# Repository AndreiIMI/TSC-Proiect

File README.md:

# TSC-Proiect
## Schema Bloc

## BOM (Bill of Materials)
| Component                            | Link | Datasheet |
|--------------------------------------|------|-----------|
| ESP32-C6-WROOM-1-N8                  | [Link](https://ro.mouser.com/ProductDetail/Espressif-Systems/ESP32-C6-WROOM-1-N8?qs=8Wlm6%252BaMh8ST02Gmwp74cw%3D%3D) | [Datasheet](https://ro.mouser.com/datasheet/2/891/Espressif_ESP32_C6_WROOM_1__Datasheet_V0_1_PRELIMI-3239987.pdf) |
| 112A-TAAR-R03_ATTEND                 | [Link](https://www.digikey.ro/ro/products/detail/attend-technology/112A-TAAR-R03/17633923) | [Datasheet](https://www.attend.com.tw/data/download/file/112A-TAAR-R03_Spec.pdf) |
| ADAFRUIT_LEDCHIP-LED0603            | [Link](https://www.snapeda.com/parts/KP-1608SURCK/Kingbright/view-part/?ref=search&t=LED%200603) | [Datasheet](https://www.snapeda.com/parts/KP-1608SURCK/Kingbright/datasheet/) |
| ESP32_WROVER_EAGLE-LTSPICE_RR0402   | [Link](https://www.snapeda.com/parts/RC0402FR-07226RL/Yageo/view-part/) | [Datasheet](https://www.snapeda.com/parts/RC0402FR-07226RL/Yageo/datasheet/) |
| ESP32_WROVER_EAGLE-LTSPICE_CC0402   | [Link](https://componentsearchengine.com/part-view/CC0402MRX5R5BB106/YAGEO) | [Datasheet](https://componentsearchengine.com/Datasheets/2/CC0402MRX5R5BB106.pdf) |
| RCL_CPOL-EUCT3528                   | [Link](https://ro.mouser.com/ProductDetail/Vishay-Sprague/TR3B106K025C1300?qs=jCGqFXxTmLdffnuDkXzk1g%3D%3D) | [Datasheet](https://www.vishay.com/docs/40080/tr3.pdf) |
| ESP32_WROVER_SPARKFUN-DISCRETESEMI_MOSFET_PCH-DMG2305UX-7 | [Link](https://ro.mouser.com/ProductDetail/Diodes-Incorporated/DMG2305UX-7?qs=L1DZKBg7t5F%2FNBHrjfxC%252Bg%3D%3D) | [Datasheet](https://www.diodes.com/assets/Datasheets/DMG2305UX.pdf) |
| 744043680IND_4828-WE-TPC_WRE        | [Link](https://www.digikey.sg/en/products/detail/w%C3%BCrth-elektronik/744043680/1638515) | [Datasheet](https://www.we-online.com/components/products/datasheet/744043680.pdf) |
| BD5229G-TR                          | [Link](https://ro.mouser.com/ProductDetail/ROHM-Semiconductor/BD5229G-TR?qs=4kLU8WoGk0vvnhrrYwdszw%3D%3D) | [Datasheet](https://fscdn.rohm.com/en/products/databook/datasheet/ic/power/voltage_detector/bd52xxg-e.pdf) |
| ESP32_WROVER_BME680_BME680          | [Link](https://ro.mouser.com/ProductDetail/Bosch-Sensortec/BME680?qs=v271MhAjFHjo0yA%2FC4OnDQ%3D%3D) | [Datasheet](https://ro.mouser.com/datasheet/2/783/BST_BME680_DS001-1509608.pdf) |
| BUTTON_CUSTOMV1                     | [Link](https://ro.mouser.com/ProductDetail/Panasonic/EVQ-P7M01P?qs=rJ%252BziJWpysz0sJAzuCybtw%3D%3D) | [Datasheet](https://industry.panasonic.com/global/en/downloads/?file_cd=402906&tab=catalog&series_cd=3457) |
| CPH3225A                             | [Link](https://ro.mouser.com/ProductDetail/Seiko-Semiconductors/CPH3225A?qs=3etwrb1wR%252BhUOph6lAO7eg%3D%3D) | [Datasheet](https://ro.mouser.com/datasheet/2/360/Seiko_Instruments_MicroBattery_E_20230330_2024Jan_-3561061.pdf) |
| DS3231SN#                            | [Link](https://ro.mouser.com/ProductDetail/Analog-Devices-Maxim-Integrated/DS3231SN?qs=1eQvB6Dk1vhUlr8%2FOrV0Fw%3D%3D) | [Datasheet](https://ro.mouser.com/datasheet/2/609/DS3231-3421123.pdf) |
| ESP32C6_VARISTORCN1812              | [Link](https://eu.mouser.com/ProductDetail/KEMET/VC1812L501R008?qs=jj7GbYRQuOa1j1%2F3gPpdvQ%3D%3D) | [Datasheet](https://eu.mouser.com/datasheet/2/447/KEM_V0002_VC-3316862.pdf) |
| ESP32_WROVER_AVX---SD0805S020S1R0_AVX_SD0805S020S1R0_0_0AVX_SD0805S020S1R0_0_0 | [Link](https://eu.mouser.com/ProductDetail/KYOCERA-AVX/SD0805S020S1R0?qs=jCA%252BPfw4LHbpkAoSnwrdjw%3D%3D&utm_id=6470900573&utm_source=google&utm_medium=cpc&utm_marketing_tactic=emeacorp&gad_source=1&gbraid=0AAAAADn_wf2CZaBvMXoqDoLB8a6wI1EC_&gclid=CjwKCAjw--K_BhB5EiwAuwYoyhyp4YPMQJxEs9O7Um1pbb_qrwD9UbwWFHYqYH_KvU5-nXs4CTfFVRoCY7kQAvD_BwE) | [Datasheet](https://eu.mouser.com/datasheet/2/40/schottky-3165252.pdf) |
| FH34SRJ-24S-0.5SH_99_               | [Link](https://eu.mouser.com/ProductDetail/Hirose-Connector/FH34SRJ-24S-05SH99?qs=vcbW%252B4%252BSTIpKBl5ap9J8Fw%3D%3D&utm_id=6470900573&utm_source=google&utm_medium=cpc&utm_marketing_tactic=emeacorp&gad_source=1&gbraid=0AAAAADn_wf2CZaBvMXoqDoLB8a6wI1EC_&gclid=CjwKCAjw--K_BhB5EiwAuwYoykKExbMK_Nf7-m2eYAFcWwWt_BaAKmDd5HmJ3DzOwus-MUIZVeL9ExoCTtAQAvD_BwE) | [Datasheet](https://eu.mouser.com/datasheet/2/185/FH34SRJ_24S_0_5SH_99__CL0580_1255_6_99_2DDrawing_0-1615044.pdf) |
| MAX17048G+T10                        | [Link](https://eu.mouser.com/ProductDetail/Analog-Devices-Maxim-Integrated/MAX17048G+T10?qs=D7PJwyCwLAoGnnn8jEPRBQ%3D%3D&utm_id=20109199409&utm_source=google&utm_medium=cpc&utm_marketing_tactic=emeacorp&gad_source=1&gbraid=0AAAAADn_wf23I7VSL8Khkvz-kjEhjYqPz&gclid=CjwKCAjw--K_BhB5EiwAuwYoytVFz576awyE1ug3GUFRWVeGavv1g_gzDMEDxxjVwp1JIOS60JmKnhoC-zIQAvD_BwE) | [Datasheet](https://eu.mouser.com/datasheet/2/609/MAX17048_MAX17049-3469099.pdf) |
| MBR0530                              | [Link](https://eu.mouser.com/ProductDetail/Micro-Commercial-Components-MCC/MBR0530-TP?qs=KFo7JewZbUECRHkxGanrdg%3D%3D&utm_id=6470900573&utm_source=google&utm_medium=cpc&utm_marketing_tactic=emeacorp&gad_source=1&gbraid=0AAAAADn_wf2CZaBvMXoqDoLB8a6wI1EC_&gclid=CjwKCAjw--K_BhB5EiwAuwYoysNC_AmHFOx6dFFFiTr86y8jRKC674aUhl0na6xIgHM9UWT_XyhG0RoCYwIQAvD_BwE) | [Datasheet](https://eu.mouser.com/datasheet/2/258/MBR0520_MBR0580_SOD123_-2492194.pdf) |
| ESP32_WROVER_SPARKFUN-IC-POWER_MCP73831 | [Link](https://ro.mouser.com/ProductDetail/Microchip-Technology/MCP73831-2DCI-MC?qs=hH%252BOa0VZEiBQ%2FrptDRXKdg%3D%3D) | [Datasheet](https://ro.mouser.com/datasheet/2/268/MCP73831_Family_Data_Sheet_DS20001984H-3441711.pdf) |
| PGB1010603MR                         | [Link](https://ro.mouser.com/ProductDetail/Littelfuse/PGB1010603MR?qs=gu7KAQ731URLg4GSnNNN7Q%3D%3D) | [Datasheet](https://www.littelfuse.com/assetdocs/pulseguard-esd-suppressors-pgb1-datasheet?assetguid=8a337998-d54d-466b-be4e-dc5bcd1f9321) |
| QWIIC_CONNECTORJS-1MM               | [Link](https://www.sparkfun.com/qwiic-jst-connector-smd-4-pin-vertical.html) | [Datasheet](https://www.jst-mfg.com/product/pdf/eng/eSH.pdf?5ec58813d214e) |
| SAMACSYS_PARTS_USB4110-GF-A         | [Link](https://eu.mouser.com/ProductDetail/GCT/USB4110-GF-A?qs=KUoIvG%2F9IlYiZvIXQjyJeA%3D%3D&utm_id=6470900573&utm_source=google&utm_medium=cpc&utm_marketing_tactic=emeacorp&gad_source=1&gbraid=0AAAAADn_wf2CZaBvMXoqDoLB8a6wI1EC_&gclid=CjwKCAjw--K_BhB5EiwAuwYoyqoFYku-1KEnaVMBZNhraqam0ThMUfxlrF7A4GQ8Pqj9d6zLqr7juBoCrOEQAvD_BwE) | [Datasheet](https://eu.mouser.com/datasheet/2/837/GCT_USB4110_Product_Drawing___20k_cycles-3455479.pdf) |
| SI1308EDL-T1-GE3                     | [Link](https://eu.mouser.com/ProductDetail/Vishay-Semiconductors/SI1308EDL-T1-GE3?qs=bX1%252BNvsK%2FBramh9tgpOaEw%3D%3D&utm_id=20109199409&utm_source=google&utm_medium=cpc&utm_marketing_tactic=emeacorp&gad_source=1&gbraid=0AAAAADn_wf23I7VSL8Khkvz-kjEhjYqPz&gclid=CjwKCAjw--K_BhB5EiwAuwYoyllRgbebqlW1QDUb9SQpEls061aMn76tZxer07jsniKXNOsDESHnSBoCkL8QAvD_BwE) | [Datasheet](https://www.vishay.com/docs/63399/si1308edl.pdf) |
| USBLC6-2SC6Y                         | [Link](https://eu.mouser.com/ProductDetail/STMicroelectronics/USBLC6-2SC6Y?qs=gNDSiZmRJS%2FOgDexvXkdow%3D%3D&srsltid=AfmBOoqlX0fgvKlHMd5oyRC9Sr6hBsf51Zi0RKmaIGejNRz6zsEP_LgY) | [Datasheet](https://eu.mouser.com/datasheet/2/389/usblc6_2sc6y-1852505.pdf) |
| SJ                                   | [Link](https://grabcad.com/library/solder-jumpers-1) | [Datasheet](https://github.com/cristiandeda/TSC_E-BookReader/blob/main) |
| W25Q512JVEIQ                         | [Link](https://eu.mouser.com/ProductDetail/Winbond/W25Q512JVEIQ?qs=l7cgNqFNU1jw6svr3at6tA%3D%3D&srsltid=AfmBOopwp-NQhQ6JM3w-WMYdzldr5QNIm_7CdLwVaaaS66y9swf4PMgu) | [Datasheet](https://eu.mouser.com/datasheet/2/949/Winbond_W25Q512JV_Datasheet-3240039.pdf) |
| XC6220A331MR-G                       | [Link](https://eu.mouser.com/ProductDetail/Torex-Semiconductor/XC6220A331MR-G?qs=AsjdqWjXhJ8ZSWznL1J0gg%3D%3D&srsltid=AfmBOopNlEzK7MdHRFabPSVSf32rb8GhsgKYTsuSlo8EjEXWvzOc5IIo) | [Datasheet](https://eu.mouser.com/datasheet/2/760/xc6220-3371556.pdf) |
## Descrierea funcționalității hardware
Această placă integrează multiple componente pentru a oferi o soluție completă de control, senzorizare și afișare cu consum redus, ideală pentru aplicații IoT.

### Alimentare și Încărcare
* #### Conector USB-C
  Oferă atât alimentare principală (5V), cât și comunicație de date.

* #### Regulator tensiune (IC1)
  Convertor step-down care aduce tensiunea de la 5V la 3.3V, necesară pentru alimentarea ESP32 și a celorlalte circuite logice.

* #### Protecție la supratensiuni (TVS - D1, PFMF.050.1)
  Diodă TVS care protejează linia de alimentare USB și comunicație împotriva descărcărilor electrostatice (ESD) și supratensiunilor.

* #### Control încărcare baterie (MCP73831)
  Circuit dedicat pentru încărcarea bateriilor Li-Po, cu protecție la supraîncărcare și descărcare. Condensatorii C1 și C2 filtrează zgomotul de pe linia de alimentare.

* #### Monitorizare baterie (MAX17048)
  Cititor de nivel al bateriei cu comunicație I2C, oferă date precise despre starea acumulatorului în timp real.

### Memorie și Stocare
* #### Memorie NOR Flash SPI (W25Q512JVEIQ)
  Stocare de 64MB pentru fișiere (imagini, texte, baze de date), conectată la ESP32 prin SPI.

* #### Cititor card SD
  Conectat pe interfață SPI (IO8–IO11), permite extinderea capacității de stocare, ideal pentru loguri sau import de fișiere externe.

### Control Principal - ESP32-C6
* #### Microcontroller ESP32-C6-WROOM-1-N8
  Nucleul principal al plăcii, gestionează toate perifericele. Suportă Wi-Fi 6, BLE 5.2, Zigbee și Thread. Dispune de GPIO-uri versatile pentru SPI, I2C, UART și control direct pentru afișajele e-paper.

### Ceas în Timp Real (RTC)
* #### DS3231SN
  Modul de ceas cu precizie ridicată, conectat prin I2C. Are o baterie de rezervă ce menține ora actualizată chiar și fără alimentare principală.

### Senzor Ambiental
* #### BME688
  Senzor avansat care măsoară temperatura, umiditatea, presiunea atmosferică și calitatea aerului. Comunicarea se face prin I2C.

### Afișaj E-Paper
* #### Header dedicat pentru E-Ink Display
  Permite conectarea unui afișaj e-paper cu consum ultra-redus.

* #### Circuit de control semnal (MBR0530, L1, Q3)
  Asigură comutarea corectă a tensiunii și semnalelor pentru afișaj.

* #### Selectare ecran
  Prin jumperul S1 se poate selecta tipul de e-paper utilizat.

### Interfețe Extinse
* #### Qwiic / Stemma QT
  Conector standard JST-SH cu 4 pini pentru adăugarea de senzori sau module I2C externe cu plug-and-play.

* #### Test Pads GPIO
  Paduri expuse pentru pini importanți ai ESP32. Ușurează depanarea, măsurătorile sau conectarea de periferice suplimentare.

### Protecție și Control
* #### Protecție ESD pe SPI & Qwiic
  Include diode TVS și rezistențe pentru protecția semnalelor împotriva descărcărilor electrostatice.

* #### Butoane de control (RESET & BOOT)
  RESET – repornește sistemul; BOOT – folosit pentru programarea ESP32. Ambele conectate la pini esențiali (EN și IO0).

## Descrierea Pinilor ESP32-C6

| **Pin ESP32-C6** | **Nume Semnal**         | **Componentă Asociată**         | **Scop / Funcție**                                                                 |
|------------------|--------------------------|----------------------------------|--------------------------------------------------------------------------------------|
| **GND**          | GND                      | Toate componentele               | Masă comună pentru alimentare și semnal.                                            |
| **EN**           | Enable                   | Buton Reset                      | Resetează microcontrollerul la apăsare.                                             |
| **IO0**          | GPIO0                    | Buton BOOT                       | Intrare în modul de boot la apăsare.                                                |

### Test & GPIO General

| **Pin ESP32-C6** | **Nume Semnal**         | **Componentă Asociată**         | **Scop / Funcție**                                                                 |
|------------------|--------------------------|----------------------------------|--------------------------------------------------------------------------------------|
| **IO1**          | GPIO1                    | Test Pad TP11                   | I/O general sau pentru debug.                                                       |
| **IO2**          | GPIO2                    | Test Pad TP12                   | I/O general sau pentru debug.                                                       |
| **IO3**          | GPIO3                    | Test Pad TP13                   | I/O general sau pentru debug.                                                       |

### Memorie NOR Flash (SPI)

| **Pin ESP32-C6** | **Nume Semnal**         | **Componentă Asociată**         | **Scop / Funcție**                                                                 |
|------------------|--------------------------|----------------------------------|--------------------------------------------------------------------------------------|
| **IO4**          | CS                       | SPI Flash (W25Q512JVEIQ)        | Chip Select pentru memoria externă.                                                |
| **IO5**          | CLK                      | SPI Flash                        | Clock SPI pentru NOR Flash.                                                        |
| **IO6**          | MISO                     | SPI Flash                        | Date din NOR Flash către ESP32.                                                    |
| **IO7**          | MOSI                     | SPI Flash                        | Date de la ESP32 către NOR Flash.                                                  |

### Card SD (SPI)

| **Pin ESP32-C6** | **Nume Semnal**         | **Componentă Asociată**         | **Scop / Funcție**                                                                 |
|------------------|--------------------------|----------------------------------|--------------------------------------------------------------------------------------|
| **IO8**          | CS                       | SD Card                          | Chip Select pentru card SD.                                                        |
| **IO9**          | CLK                      | SD Card                          | Clock SPI pentru card SD.                                                          |
| **IO10**         | MISO                     | SD Card                          | Date de pe card SD către ESP32.                                                    |
| **IO11**         | MOSI                     | SD Card                          | Date de la ESP32 către card SD.                                                    |

### E-Paper Display

| **Pin ESP32-C6** | **Nume Semnal**         | **Componentă Asociată**         | **Scop / Funcție**                                                                 |
|------------------|--------------------------|----------------------------------|--------------------------------------------------------------------------------------|
| **IO12**         | BUSY / RST / etc.        | E-Paper Header                   | Semnale de control pentru afișaj.                                                  |
| **IO13**         | -                        | E-Paper Header                   | Semnal suplimentar pentru afișaj.                                                  |
| **IO14**         | -                        | E-Paper Header                   | Semnal suplimentar pentru afișaj.                                                  |
| **IO15**         | -                        | E-Paper Header                   | Semnal suplimentar pentru afișaj.                                                  |

### Magistrală I2C (RTC & Senzor Mediu)

| **Pin ESP32-C6** | **Nume Semnal**         | **Componentă Asociată**         | **Scop / Funcție**                                                                 |
|------------------|--------------------------|----------------------------------|--------------------------------------------------------------------------------------|
| **IO16**         | SCL                      | RTC (DS3231), BME688             | Clock pentru comunicația I2C.                                                      |
| **IO17**         | SDA                      | RTC (DS3231), BME688             | Date pentru comunicația I2C.                                                       |

### Serial Debug / Qwiic

| **Pin ESP32-C6** | **Nume Semnal**         | **Componentă Asociată**         | **Scop / Funcție**                                                                 |
|------------------|--------------------------|----------------------------------|--------------------------------------------------------------------------------------|
| **IO18**         | UART_RX                  | Qwiic / Debug Header             | Recepție serială (ex: debugging, interfață Qwiic).                                  |
| **IO19**         | UART_TX                  | Qwiic / Debug Header             | Transmisie serială.                                                                 |

## Pași de Implementare

1. **Proiectarea Schemei**
   - Am realizat schema electrică folosind componente din biblioteca specificată.
   - Am verificat schema cu ERC și am rezolvat toate erorile relevante.
   - M-am asigurat că toate componentele au footprint corect și conexiuni valide.

2. **Plasarea Componentelor pe PCB**
   - Am plasat toate componentele exclusiv pe layer-ul **TOP**, conform cerințelor.
   - Am amplasat corect condensatoarele de decuplare (100nF) lângă pinii de alimentare.
   - Am poziționat antena modulului ESP32 spre exteriorul plăcii și am decupat zona de sub ea.
   - Am ignorat erorile de dimension generate de butoane și mufa USB, conform instrucțiunilor.

3. **Rutarea PCB-ului**
   - Am rutat traseele de alimentare cu **width = 0.3mm** și cele de semnal cu **minim 0.15mm**.
   - Am evitat unghiurile drepte și am minimizat utilizarea de vias-uri pe traseele de putere.
   - Fiind o placă dublu strat, am aplicat **via stitching** între planurile de masă.
   - Nu am rutat trasee sub antena ESP32 și am decupat zona PCB-ului din acea regiune.

4. **Verificare și Validare**
   - Am folosit fișierul de verificare pentru DRC și am corectat toate problemele importante.
   - Am ignorat eroarea “Only INPUT pins on NET ID” conform indicațiilor.
   - Am marcat clar toate test pad-urile în silkscreen cu denumirile semnalelor (ex. MOSI, RX).

5. **Realizarea Silkscreen-ului**
   - Am păstrat silkscreen-ul clar și lizibil, cu **numele componentelor**, fără valorile acestora.

6. **Modelarea 3D**
   - Am importat modelul 3D al PCB-ului în carcasa furnizată.
   - Am desenat bateria și ecranul conform dimensiunilor mecanice din datasheet-uri.

7. **Generarea Fișierelor Finale**
   - Am generat fișierele **Gerber** conform tutorialului oferit.
   - Am creat fișierele **BOM** și **Pick and Place** pentru fabricație, urmând pașii din tutorial.
   - Pentru componente și modele 3D, am folosit [Component Search Engine](https://componentsearchengine.com).

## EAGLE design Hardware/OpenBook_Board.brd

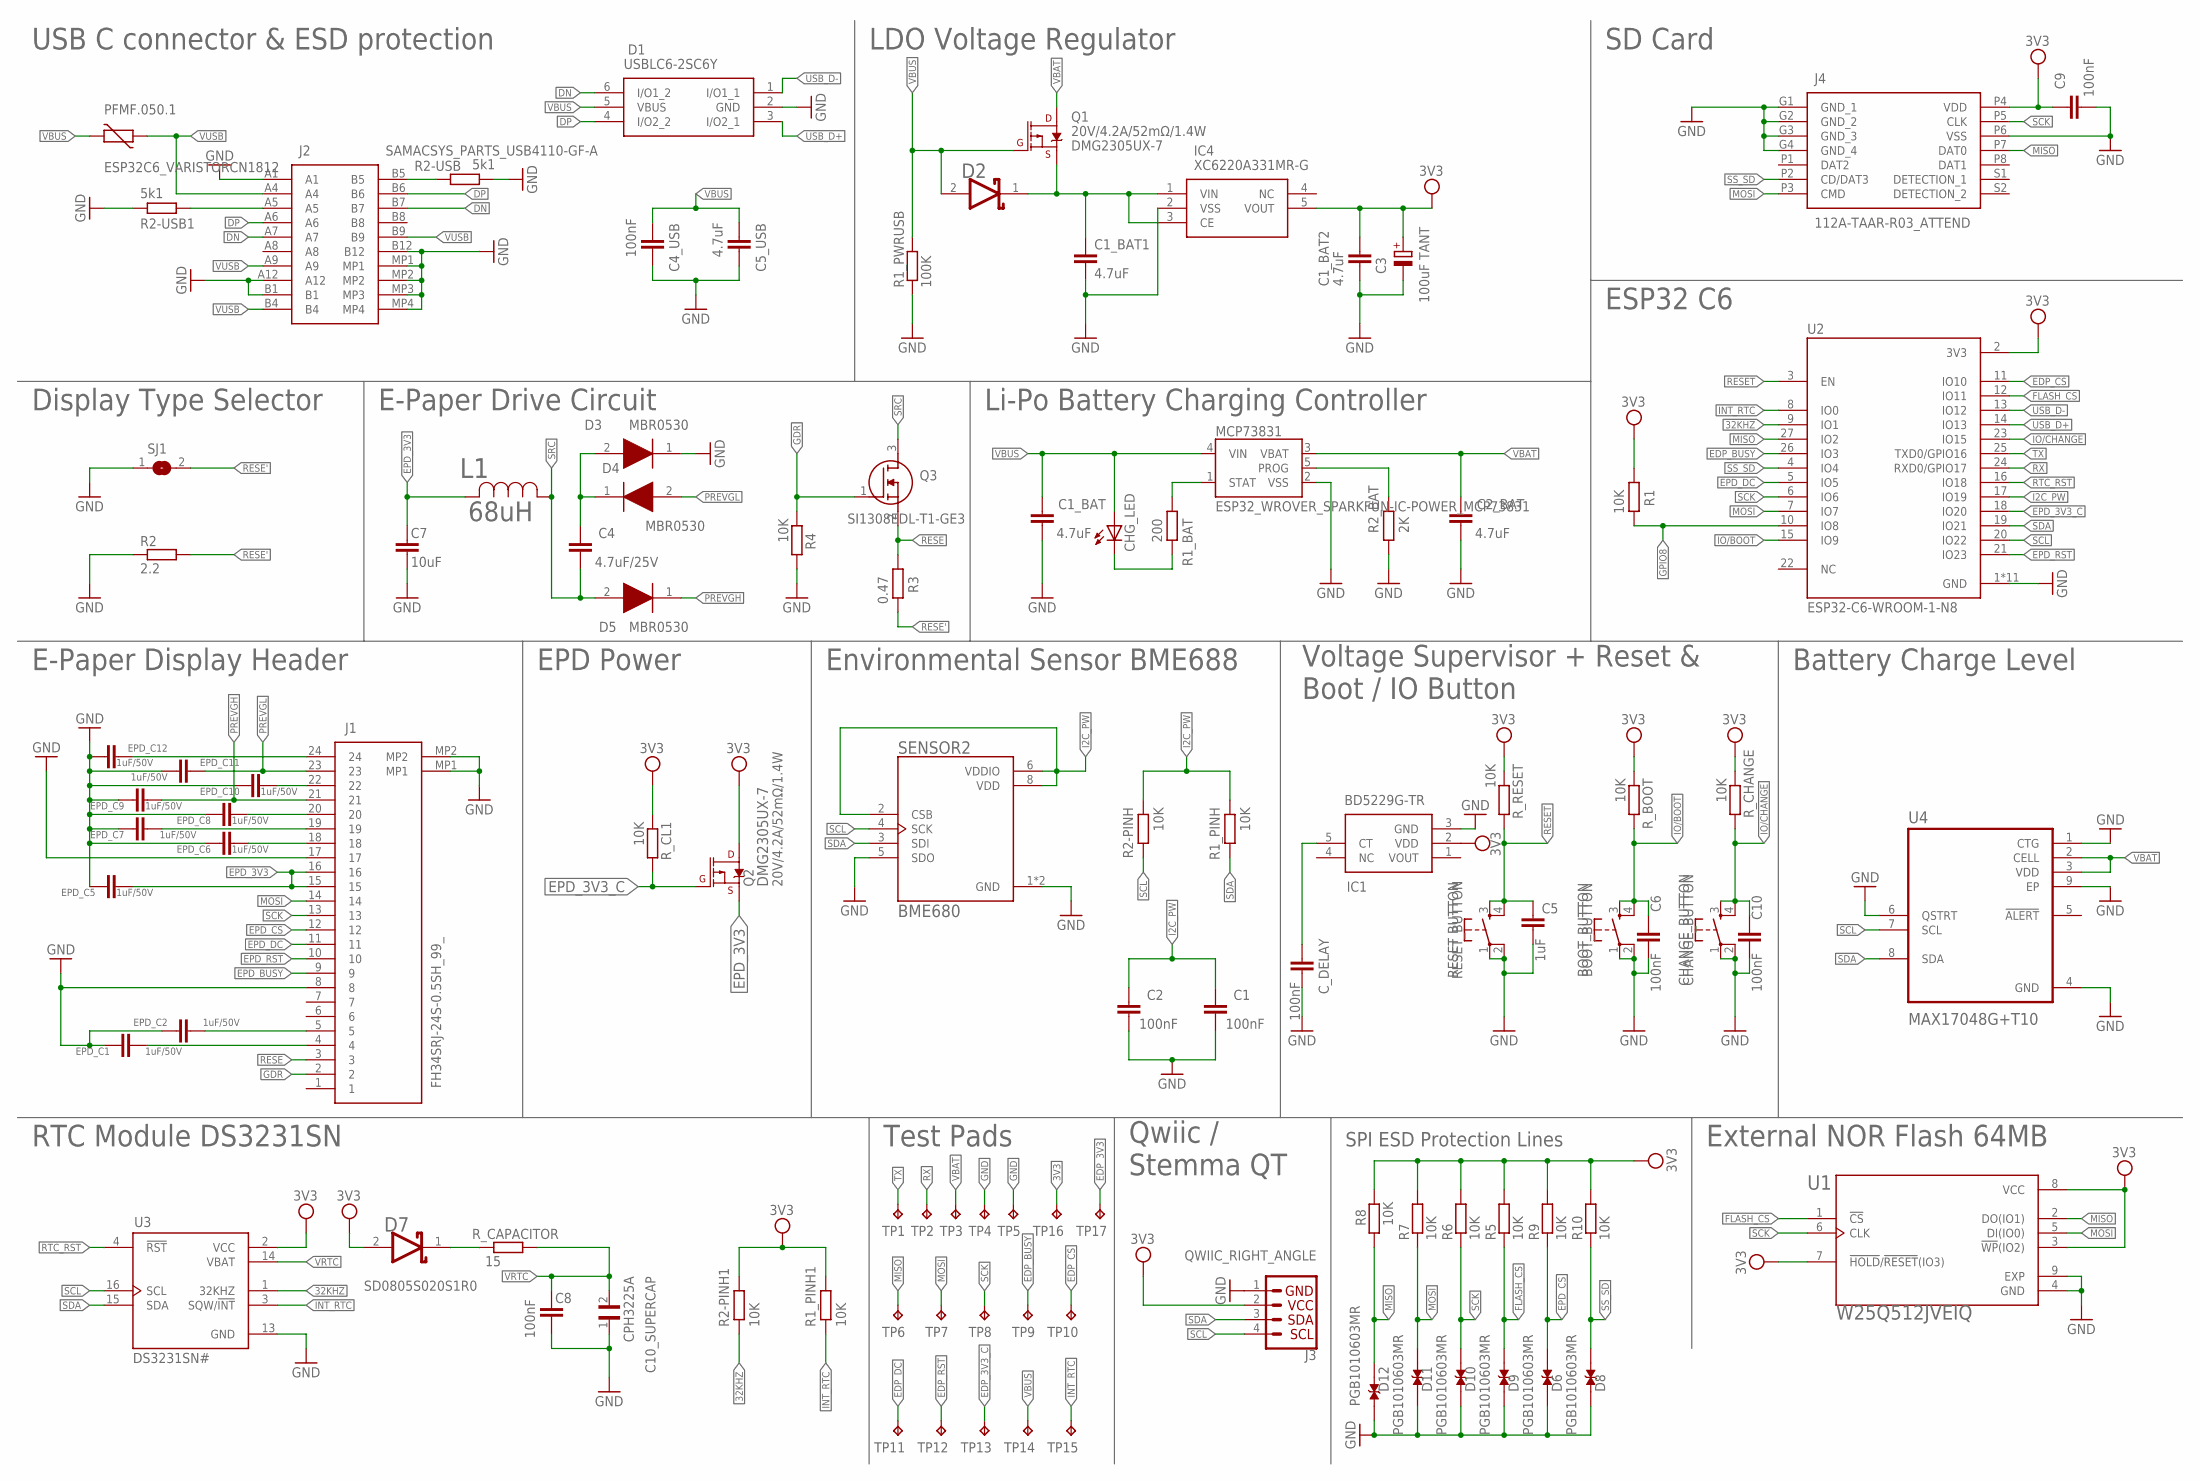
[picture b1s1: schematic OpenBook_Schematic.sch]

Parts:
BOOT_BUTTON: BOOT_BUTTON; MYBUTTON
C1, C2, C4_USB, C6, C8, C9, C10: 100nF; EAGLE-LTSPICE_C0402
C1_BAT, C1_BAT1, C1_BAT2, C2_BAT, C5_USB: 4.7uF; EAGLE-LTSPICE_C0402
C3: 100uF TANT; RCL_CT3528
C4: 4.7uF/25V; EAGLE-LTSPICE_C0402
C5: 1uF; EAGLE-LTSPICE_C0402
C7: 10uF; EAGLE-LTSPICE_C0402
C10_SUPERCAP: CPH3225A; CAPCP3225X100N
CHANGE_BUTTON: CHANGE_BUTTON; MYBUTTON
CHG_LED: ADAFRUIT_LEDCHIP-LED0603; ADAFRUIT_CHIP-LED0603
C_DELAY: 100nF; EAGLE-LTSPICE_C0402
D1: USBLC6-2SC6Y; SOT95P280X145-6N
D2, D7: ESP32_WROVER_AVX---SD0805S020S1R0_AVX_SD0805S020S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; ESP32_WROVER_AVX---SD0805S020S1R0_AVX_SD0805S020S1R0_0
D3, D4, D5: MBR0530; SOD3716X135N
D6, D8, D9, D10, D11, D12: PGB1010603MR; DIOC1608X36N
EPD_C1, EPD_C2, EPD_C5, EPD_C6, EPD_C7, EPD_C8, EPD_C9, EPD_C10, EPD_C11, EPD_C12: 1uF/50V; EAGLE-LTSPICE_C0402
IC1: BD5229G-TR; SOT95P280X120-5N
IC4: XC6220A331MR-G; SOT95P280X120-5N
J1: FH34SRJ-24S-0.5SH_99_; FH34SRJ24S05SH99
J2: SAMACSYS_PARTS_USB4110-GF-A; SAMACSYS_PARTS_USB4110GFA
J3: QWIIC_RIGHT_ANGLE; JST04_1MM_RA
J4: 112A-TAAR-R03_ATTEND; 112ATAARR03ATTEND
L1: 68uH; IND_4828-WE-TPC_WRE
MCP73831: ESP32_WROVER_SPARKFUN-IC-POWER_MCP73831; ESP32_WROVER_SPARKFUN-IC-POWER_SOT23-5
PFMF.050.1: ESP32C6_VARISTORCN1812; ESP32C6_VARISTOR_CT/CN1812
Q1, Q2: 20V/4.2A/52mΩ/1.4W; ESP32_WROVER_SPARKFUN-DISCRETESEMI_SOT23-3
Q3: SI1308EDL-T1-GE3; SOT65P210X110-3N
R1, R1_PINH, R1_PINH1, R2-PINH, R2-PINH1, R4, R5, R6, R7, R8, R9, R10: 10K; ESP32_WROVER_EAGLE-LTSPICE_R0402
R1_BAT: 200; ESP32_WROVER_EAGLE-LTSPICE_R0402
R1_PWRUSB: 100K; ESP32_WROVER_EAGLE-LTSPICE_R0402
R2: 2.2; ESP32_WROVER_EAGLE-LTSPICE_R0402
R2-USB, R2-USB1: 5k1; ESP32_WROVER_EAGLE-LTSPICE_R0402
R2_BAT: 2K; ESP32_WROVER_EAGLE-LTSPICE_R0402
R3: 0.47; ESP32_WROVER_EAGLE-LTSPICE_R0402
RESET_BUTTON: RESET BUTTON; MYBUTTON
R_BOOT: 10K; ESP32_WROVER_EAGLE-LTSPICE_R0402
R_CAPACITOR: 15; ESP32_WROVER_EAGLE-LTSPICE_R0402
R_CHANGE: 10K; ESP32_WROVER_EAGLE-LTSPICE_R0402
R_CL1: 10K; ESP32_WROVER_EAGLE-LTSPICE_R0402
R_RESET: 10K; ESP32_WROVER_EAGLE-LTSPICE_R0402
SENSOR2: BME680; ESP32_WROVER_BME680_PSON80P300X300X100-8N
SJ1: SJ
TP1, TP2, TP3, TP4, TP5, TP6, TP7, TP8, TP9, TP10, TP11, TP12, TP13, TP14, TP15, TP16, TP17: TPTP20R; TP20R
U1: W25Q512JVEIQ; SON127P600X800X80-9N
U2: ESP32-C6-WROOM-1-N8; XCVR_ESP32-C6-WROOM-1-N8
U3: DS3231SN#; SOIC127P1032X265-16N
U4: MAX17048G+T10; SON50P200X200X80-9N

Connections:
3V3: C1_BAT2.1, C3.+, C9.1, D7.2 (ANODE), IC1.2 (VDD), IC4.5 (VOUT), J3.2, J4.P4 (VDD), Q2.3 (D), R1.1, R1_PINH1.2, R2-PINH1.2, R5.2, R6.2, R7.2, R8.2, R9.2, R10.2, R_BOOT.1, R_CHANGE.1, R_CL1.1, R_RESET.1, TP16.TP, U1.3 (!WP!(IO2)), U1.7 (!HOLD!/!RESET!(IO3)), U1.8 (VCC), U2.2 (3V3), U3.2 (VCC)
32KHZ: R2-PINH1.1, U2.9 (IO1), U3.1 (32KHZ)
DN: D1.6 (I/O1_2), J2.A7, J2.B7
DP: D1.4 (I/O2_2), J2.A6, J2.B6
EDP_3V3: TP17.TP
EDP_3V3_C: TP13.TP
EDP_BUSY: TP9.TP, U2.26 (IO3)
EDP_CS: TP10.TP, U2.11 (IO10)
EDP_DC: TP11.TP
EDP_RST: TP12.TP
EPD_3V3: C7.1, EPD_C5.1, J1.15, J1.16, L1.2, Q2.2 (S)
EPD_3V3_C: Q2.1 (G), R_CL1.2, U2.18 (IO20)
EPD_BUSY: J1.9
EPD_CS: D6.2, J1.12, R9.1
EPD_DC: J1.11, U2.5 (IO5)
EPD_RST: J1.10, U2.21 (IO23)
FLASH_CS: D9.2, R5.1, U1.1 (!CS), U2.12 (IO11)
GDR: J1.2, Q3.1 (G), R4.1
GND: BOOT_BUTTON.1, BOOT_BUTTON.2, C1.2, C1_BAT.2, C1_BAT1.2, C1_BAT2.2, C2.2, C2_BAT.2, C3.-, C4_USB.2, C5.2, C5_USB.2, C6.2, C7.2, C8.2, C9.2, C10.2, C10_SUPERCAP.1, CHANGE_BUTTON.1, CHANGE_BUTTON.2, C_DELAY.2, D1.2 (GND), D3.1 (K), D6.1, D8.1, D9.1, D10.1, D11.1, D12.1, EPD_C1.2, EPD_C2.2, EPD_C5.2, EPD_C6.2, EPD_C7.2, EPD_C8.2, EPD_C9.2, EPD_C10.2, EPD_C11.2, EPD_C12.2, IC1.3 (GND), IC4.2 (VSS), J1.8, J1.17, J1.MP1, J1.MP2, J2.A1, J2.A12, J2.B1, J2.B12, J2.MP1, J2.MP2, J2.MP3, J2.MP4, J3.1, J4.G1 (GND_1), J4.G2 (GND_2), J4.G3 (GND_3), J4.G4 (GND_4), J4.P6 (VSS), MCP73831.2 (VSS), R1_PWRUSB.1, R2.1, R2-USB.2, R2-USB1.1, R2_BAT.1, R4.2, RESET_BUTTON.1, RESET_BUTTON.2, SENSOR2.1 (GND), SENSOR2.5 (SDO), SENSOR2.7 (GND), SJ1.1, TP4.TP, TP5.TP, U1.4 (GND), U1.9 (EXP), U2.1 (GND), U2.28 (GND), U2.29_1 (GND), U2.29_2 (GND), U2.29_3 (GND), U2.29_4 (GND), U2.29_5 (GND), U2.29_6 (GND), U2.29_7 (GND), U2.29_8 (GND), U2.29_9 (GND), U3.13 (GND), U4.1 (CTG), U4.4 (GND), U4.6 (QSTRT), U4.9 (EP)
GPIO8: R1.2, U2.10 (IO8)
I2C_PW: C1.1, C2.1, R1_PINH.1, R2-PINH.1, SENSOR2.2 (CSB), SENSOR2.6 (VDDIO), SENSOR2.8 (VDD), U2.17 (IO19)
INT_RTC: R1_PINH1.1, TP15.TP, U2.8 (IO0), U3.3 (SQW/!INT)
IO/BOOT: BOOT_BUTTON.3, BOOT_BUTTON.4, C6.1, R_BOOT.2, U2.15 (IO9)
IO/CHANGE: C10.1, CHANGE_BUTTON.3, CHANGE_BUTTON.4, R_CHANGE.2, U2.23 (IO15)
MISO: D12.2, J4.P7 (DAT0), R8.1, TP6.TP, U1.2 (DO(IO1)), U2.27 (IO2)
MOSI: D11.2, J1.14, J4.P3 (CMD), R7.1, TP7.TP, U1.5 (DI(IO0)), U2.7 (IO7)
unnamed: J2.A5, R2-USB1.2
unnamed: C1_BAT1.1, D2.1 (CATHODE), IC4.1 (VIN), IC4.3 (CE), Q1.2 (S)
unnamed: MCP73831.1 (STAT), R1_BAT.1
unnamed: J2.B5, R2-USB.1
unnamed: CHG_LED.C, R1_BAT.2
unnamed: EPD_C12.1, J1.24
unnamed: MCP73831.5 (PROG), R2_BAT.2
unnamed: C4.1, D3.2 (A), D4.1 (K)
unnamed: C_DELAY.1, IC1.5 (CT)
unnamed: EPD_C10.1, J1.22
unnamed: EPD_C8.1, J1.20
unnamed: EPD_C7.1, J1.19
unnamed: EPD_C6.1, J1.18
unnamed: EPD_C2.1, J1.5
unnamed: EPD_C1.1, J1.4
unnamed: D7.1 (CATHODE), R_CAPACITOR.2
PREVGH: D5.1 (K), EPD_C9.1, J1.21
PREVGL: D4.2 (A), EPD_C11.1, J1.23
RESE: J1.3, Q3.2 (S), R3.1
RESE': R2.2, R3.2, SJ1.2
RESET: C5.1, RESET_BUTTON.3, RESET_BUTTON.4, R_RESET.2, U2.3 (EN)
RTC_RST: U2.16 (IO18), U3.4 (!RST)
RX: TP2.TP, U2.24 (RXD0/GPIO17)
SCK: D10.2, J1.13, J4.P5 (CLK), R6.1, TP8.TP, U1.6 (CLK), U2.6 (IO6)
SCL: J3.4, R2-PINH.2, SENSOR2.4 (SCK), U2.20 (IO22), U3.16 (SCL), U4.7 (SCL)
SDA: J3.3, R1_PINH.2, SENSOR2.3 (SDI), U2.19 (IO21), U3.15 (SDA), U4.8 (SDA)
SRC: C4.2, D5.2 (A), L1.1, Q3.3 (D)
SS_SD: D8.2, J4.P2 (CD/DAT3), R10.1, U2.4 (IO4)
TX: TP1.TP, U2.25 (TXD0/GPIO16)
USB_D+: D1.3 (I/O2_1), U2.14 (IO13)
USB_D-: D1.1 (I/O1_1), U2.13 (IO12)
VBAT: C2_BAT.1, MCP73831.3 (VBAT), Q1.3 (D), TP3.TP, U4.2 (CELL), U4.3 (VDD)
VBUS: C1_BAT.1, C4_USB.1, C5_USB.1, CHG_LED.A, D1.5 (VBUS), D2.2 (ANODE), MCP73831.4 (VIN), PFMF.050.1.2, Q1.1 (G), R1_PWRUSB.2, TP14.TP
VRTC: C8.1, C10_SUPERCAP.2, R_CAPACITOR.1, U3.14 (VBAT)
VUSB: J2.A4, J2.A9, J2.B4, J2.B9, PFMF.050.1.1

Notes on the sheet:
USB C connector & ESD protection
LDO Voltage Regulator
DMG2305UX-7
SD Card
Display Type Selector
E-Paper Drive Circuit
Li-Po Battery Charging Controller
ESP32 C6
E-Paper Display Header
EPD Power
Environmental Sensor BME688
Voltage Supervisor + Reset & Boot / IO Button
Battery Charge Level
RTC Module DS3231SN
SD0805S020S1R0
Test Pads
Qwiic / Stemma QT
SPI ESD Protection Lines
External NOR Flash 64MB

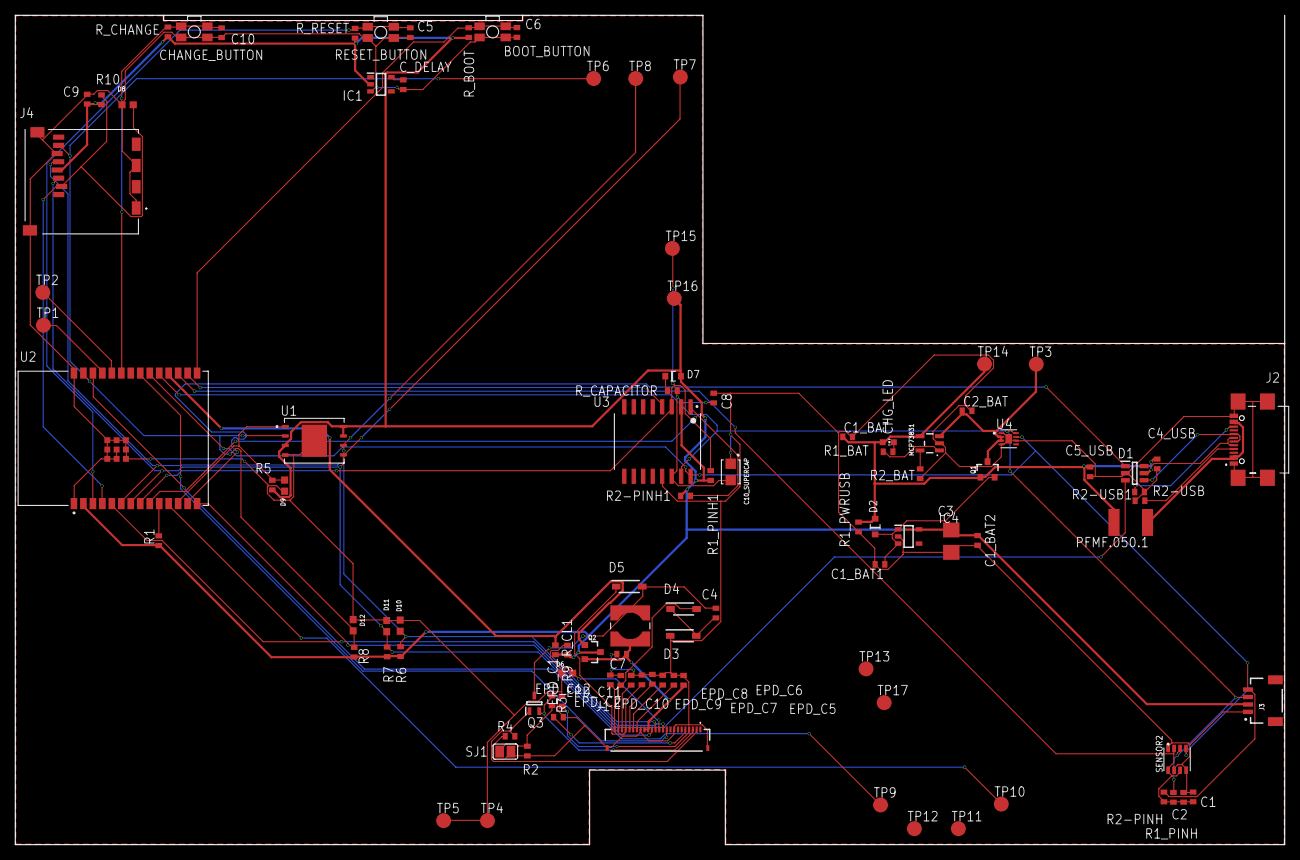
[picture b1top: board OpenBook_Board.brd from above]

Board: 2 copper layers, 170.2 x 111.2 mm, 103 parts (0 on the bottom side), 56 nets.

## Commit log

2025-04-06 Added EVT
2025-04-06 Create LICENSE
2025-04-15 Fixes

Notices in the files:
parts and their libraries:
COPYRIGHT: Copyright (C) 2024 Ultra Librarian. All rights reserved.
